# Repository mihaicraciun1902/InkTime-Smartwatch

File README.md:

# ⌚ InkTime: Open-Source Hackable Smartwatch

**InkTime** is an affordable, open-source smartwatch powered by the Nordic nRF52840 SoC and an ultra-low-power e-paper display. It is designed from the ground up to be highly hackable, easy to manufacture, and power-efficient.

This repository contains all Engineering Validation (EVT) and Design Validation (DVT) files, including schematics, PCB layouts, 3D mechanical models, and manufacturing files.

---

## 🏗️ 1. System Architecture (Block Diagram)

The following diagram illustrates the core components of the InkTime hardware and their data/power relationships:

```text
                     +---------------------------------------------------+
                     |               nRF52840 SoC (U$1)                  |
                     |          ARM Cortex-M4F @ 64 MHz                  |
                     |    BLE 5.0 | 1MB Flash | 256KB RAM | USB 2.0      |
                     +---------------------------------------------------+
                              |                 |                  |
       [ SPI & GPIO ]---------+                 |                  +--------[ I2C Bus ]
       |                                        |                  |
+-------------------+                           |           +-------------------+
| E-Paper Display   |                           |           | BQ25180 (Charger) |<-- USB VBUS
| 24-pin FPC (J2)   |                           |           +-------------------+
+-------------------+       [ Push Buttons ]----+           | MAX17048 (Fuel)   |<-- LiPo Cell
                            | SW_UP (P0.13)     |           +-------------------+
+-------------------+       | SW_ENT (P0.14)    |           | BMA423 (IMU)      |
| Power Management  |       | SW_DN (P1.02)     |           +-------------------+
| RT6160A 3.3V Reg. |       +-------------------+           | DRV2605 (Haptic)  |
+-------------------+                                       +-------------------+
```

## 🧩 2. Hardware Implementation & Functionality

The hardware is designed on a 1mm thick, 2-layer PCB to fit strictly within the mechanical constraints of the provided case. All component placement is restricted to the TOP layer, with dual ground planes and extensive via stitching.

### Core Processing & Connectivity (nRF52840)

The heart of the watch is the nRF52840-QIAA. It handles all BLE 5.0 communication, USB 2.0 Full-Speed interfacing, and peripheral management.

- **Clocks:** Requires a 32 MHz crystal (X1) for the RF HFXO and a 32.768 kHz crystal (X2) for the RTC/LFXO deep sleep timekeeping.
- **RF Layout:** The 2.4 GHz chip antenna (Johanson 2450AT18B100E) is edge-mounted. Per Nordic guidelines, the PCB is physically cut out directly beneath the antenna, with a strict keepout zone (no copper, no routing).

### Display System

We utilize an e-paper display connected via a 24-pin 0.5mm FPC connector.

- **Interface:** 4-wire SPI + GPIO control (DC, RST, BUSY).
- **Power:** Driven by an independent 3.3V boost converter (L1). Power is gated by a P-channel MOSFET (Q1) via the `EPD_PWR` pin, ensuring zero current draw when the display is not refreshing.

### Power Management & Battery (BQ25180 + RT6160A)

- **Charging:** The BQ25180 manages charging from the USB-C VBUS. It is compact and entirely I2C-configurable. The charge current is hardware-set to 100mA via a 10kΩ resistor.
- **Regulation:** The RT6160A buck-boost converter takes the variable LiPo voltage (3.0V - 4.2V) and provides a stable 3.3V system rail.
- **Clearance hack:** To meet strict Z-axis constraints of the case, the JST connector was omitted; the LiPo cell is soldered directly to `TP_VBAT` and `TP_BAT_GND`.

### Sensors & Actuators

- **IMU (BMA423):** A 3-axis accelerometer with a built-in hardware step counter and wrist-tilt detection. It uses hardware interrupts (`IMU_INT1`, `IMU_INT2`) to wake the nRF from deep sleep, saving processing power.
- **Haptics (DRV2605):** Drives an ERM/LRA vibration motor. The `HAPTIC_EN` pin physically disables the driver during sleep to eliminate quiescent current leakage.

## 📌 3. nRF52840 Pin Mapping

Pins were carefully selected to group peripheral buses (like SPI and I2C) physically close to their target ICs, minimizing trace lengths.

| Pin                     | Signal            | Destination      | Function & Justification |
|-------------------------|-------------------|------------------|--------------------------|
| P0.02                   | SCK               | EPD (J2)         | SPI Clock. SPIM is remappable; chosen for routing ease. |
| P0.03                   | MOSI              | EPD (J2)         | SPI Data Out. Grouped with SCK to minimize trace length. |
| P0.05                   | EPD_CS            | EPD (J2)         | SPI Chip Select for e-paper. |
| P0.06                   | SDA               | I2C Bus          | I2C Data. Placed close to BQ25180 & BMA423 to keep traces short. |
| P0.07                   | SCL               | I2C Bus          | I2C Clock. |
| P0.08                   | IMU_INT1          | BMA423           | Hardware wake interrupt from accelerometer. |
| P0.11                   | PMIC_INT          | BQ25180          | Interrupt for battery charge state changes. |
| P0.12                   | HAPTIC_EN         | DRV2605          | GPIO output to hard-disable haptic driver during sleep. |
| P0.13 / P0.14 / P1.02   | SW_UP / ENT / DN  | Tactile Switches | GPIO inputs with hardware debouncing (10kΩ pull-up + 1µF low-pass). |
| P1.01                   | EPD_PWR           | Q1 Gate          | EPD power rail enable switch. |

## 🔋 4. Power Consumption Analysis

The system is highly optimized for deep sleep. Based on component datasheets, estimated battery life on a 180mAh LiPo cell is approximately 5-7 days.

| Mode                  | nRF52840 | Display | Sensors/Other | Total |
|-----------------------|----------|---------|---------------|-------|
| System OFF (Sleep)    | 2.5 µA   | 0 mA    | 0.5 µA        | ~3 µA |
| BLE Advertising (1s)  | ~15 mA   | 0 mA    | 0.13 mA       | ~15 mA |
| Display Refresh       | ~3 mA    | ~30 mA  | 0.13 mA       | ~33 mA |
| Haptic Feedback       | ~5 mA    | 0 mA    | ~60 mA        | ~65 mA |

## 🧾 5. Bill of Materials (BOM)

Updated from Fusion Hub partlist export (Project: **Proiect TSC**, Board: **PCB**, Date: **21/04/2026 4:52 PM**).

| Qty | Value / MPN | Device / Package | Parts | Description |
|-----|-------------|------------------|-------|-------------|
| 1 | ESP32_C6_LIBRARY_7_JUMPER_SJ | ESP32_C6_LIBRARY_7_JUMPER_SJ | SJ1 | SMD solder jumper |
| 3 | 0 / CPF0201D7K68C1 | CPF0201D7K68C1_0201 | R2, R3, R4 | 7.68k thin film resistor, 0201 |
| 2 | 0.1uF / GRM011R60J152KE01L | CAPC0201X13N | C23, C42 | Murata capacitor |
| 3 | 0.1uF | NORDIC_NRF_3_RESC0201_L | C27, C34, EPD_C5 | Generic chip capacitor |
| 1 | 0.47 / CPF0201D7K68C1 | CPF0201D7K68C1_0201 | R1_EP_DR | 0201 thin film resistor |
| 1 | 1.0uF | NORDIC_NRF_3_RESC0201_L | C15 | Generic chip capacitor |
| 5 | 100nF | NORDIC_NRF_3_RESC0201_L | C5, C7, C8, C12, C19 | Generic chip capacitor |
| 1 | 100pF | NORDIC_NRF_3_RESC0201_L | C11 | Generic chip capacitor |
| 2 | 10K / CPF0201D7K68C1 | CPF0201D7K68C1_0201 | R2_EP_DR, R_PWR_EPD | 0201 thin film resistor |
| 4 | 10k / CPF0201D7K68C1 | CPF0201D7K68C1_0201 | R5, R7, R8, R9 | 0201 thin film resistor |
| 3 | 10uF | NORDIC_NRF_3_RESC0201_L | C1-EP-DR, C24, C39 | Generic chip capacitor |
| 1 | 10uH | NORDIC_NRF_2_RESC0402_L | L2 | Generic chip inductor |
| 4 | 12pF | NORDIC_NRF_3_RESC0201_L | C1, C2, C17, C18 | Generic chip capacitor |
| 1 | 15nH | NORDIC_NRF_2_RESC0402_L | L3 | Generic chip inductor |
| 2 | 1pF | NORDIC_NRF_3_RESC0201_L | C3, C4 | Generic chip capacitor |
| 2 | 1uF / GRM011R60J152KE01L | CAPC0201X13N | C37, C38 | Murata capacitor |
| 9 | 1uF | NORDIC_NRF_3_RESC0201_L | EPD_C1, EPD_C2, EPD_C6, EPD_C7, EPD_C8, EPD_C9, EPD_C10, EPD_C11, EPD_C12 | Generic chip capacitor |
| 4 | 1uF | NORDIC_NRF_3_RESC0402_L | C29, C30, C31, C32 | Generic chip capacitor |
| 1 | 2.2 / CPF0201D7K68C1 | CPF0201D7K68C1_0201 | R_TYPE_SEL | 0201 thin film resistor |
| 3 | EVP-AKE31A | SW_EVP-AKE31A_PAN | SW_DN, SW_ENT, SW_UP | Panasonic tactile switch |
| 1 | DMG2305UX-7 | SOT23-3 | Q1 | P-channel MOSFET (20V/4.2A/52mΩ) |
| 2 | 22uF | NORDIC_NRF_3_RESC0201_L | C25, C33 | Generic chip capacitor |
| 1 | 3.9nH | NORDIC_NRF_2_RESC0201_M | L1 | Generic chip inductor |
| 1 | 9HT10-32.768KDZF-T | XTAL330X1051X90N | X2 | 32.768kHz crystal |
| 1 | 32MHz | NORDIC_NRF_BT-XTAL_2016_N | X1 | 32MHz crystal |
| 2 | 3k3 / CPF0201D7K68C1 | CPF0201D7K68C1_0201 | R17, R18 | 0201 thin film resistor |
| 6 | 4.7uF | NORDIC_NRF_3_RESC0201_L | C2-EP-DR, C6, C14, C20, C21, C43 | Generic chip capacitor |
| 1 | 2450AT18B100E | ANTC3216X140N | ANT1 | 2.45GHz chip antenna |
| 1 | 47nF | NORDIC_NRF_3_RESC0201_L | C16 | Generic chip capacitor |
| 1 | 744043680 | IND_4828-WE-TPC_WRE | L5 | Wurth inductor, 48uH |
| 1 | 503480-2400 | 5034802400 | J1 | 24-pin 0.5mm FPC connector |
| 2 | 5k1 / CPF0201D7K68C1 | CPF0201D7K68C1_0201 | R1_USB, R2_USB | 0201 thin film resistor |
| 1 | 820pF | NORDIC_NRF_3_RESC0201_L | C9 | Generic chip capacitor |
| 1 | BMA423 | BMA423_BMA423 | IC3 | 3-axis accelerometer |
| 1 | BQ25180YBGR | BGA8C40P2X4_100X155X50 | IC1 | Li-ion/LiFePO4 charger IC |
| 1 | FTC252012SR47MBCA | INDC2016X100N | L7 | 0.47uH inductor |
| 14 | HECTOR_WATCH_1_TPTP20R | HECTOR_WATCH_1_TP20R | TP_3.3V, TP_3V3, TP_BAT_GND, TP_GND, TP_ON, TP_OP, TP_RESET, TP_SCL, TP_SDA, TP_SWDIO, TP_SWD_CLK, TP_SWO, TP_VBAT, TP_VREG | Test pads |
| 1 | KH-TYPE-C-16P | KH-TYPE-C-16P_KINGHELM_KH-TYPE-C-16P | J4 | USB-C 16-pin connector |
| 1 | MAX17048G+T10 | SON50P200X200X80-9N | U3 | 1-cell/2-cell fuel gauge |
| 3 | MBR0530 | SOD3716X135N | D2, D4, D5 | Schottky diode 30V 0.5A |
| 3 | N.C. | NORDIC_NRF_3_RESC0201_L | C10, C13, C22 | DNI capacitor footprints |
| 1 | NRF52840_QF | AQFN50P700X700X85_HS-74N | U1 | nRF52840 SoC |
| 1 | RT6160AWSC | BGA15C40P3X5_140X230X60 | IC9 | Buck-boost regulator |
| 1 | DRV2605YZFR | BGA9C50P3X3_144X144X62 | IC2 | Haptic driver |
| 1 | SI1308EDL-T1-GE3 | SOT65P210X110-3N | Q3 | N-channel MOSFET |
| 1 | TC2030-IDC | TC2030IDC | J2 | 6-pos cable adapter |
| 1 | USBLC6-2SC6Y | SOT95P280X145-6N | D3 | USB ESD TVS protection array |

## 🛠️ 6. Design Log & Constraint Compliance (Review Notes)

This design strictly follows the DVT guidelines and mechanical constraints. Below are key design decisions and ignored rule exceptions intended for the reviewer:

- **1mm PCB thickness:** Reduced from standard 1.6mm to ensure vertical mechanical clearance inside the provided STEP case.
- **TOP-layer-only placement:** All SMDs and ICs are strictly placed on the TOP layer. Both layers feature grounded copper pours, heavily via-stitched (especially near the RF path).
- **Trace widths & geometry:** Power nets (`3V3`, `VBAT`, `VBUS`, `VREG`) are routed at 0.3mm. Data signals use 0.15mm. Trace neck-down is only utilized under BGA pads. 90-degree angles were avoided; all corners use 45-degree chamfers.
- **Decoupling proximity:** Every 100nF decoupling capacitor is placed immediately adjacent (within one pad length) to its respective IC power pin on the TOP layer.
- **RF keepout & substrate:** The area under the 2450AT18B100E antenna is entirely void of copper on both layers, and features a physical PCB cutout per Nordic reference design.
- **Accepted ERC warning:** "Only INPUT pins on NET ID" is present but ignored as a known false-positive in the CAD tool, approved by project guidelines.
- **Accepted DRC errors:** Dimension errors near the three tactile buttons and the USB-C aperture are intentional structural slots required for casing alignment.
- **Silkscreen integrity:** Test pads (`TP_3V3`, `TP_SWDIO`, etc.) are clearly labeled in silkscreen. Component values are hidden to maintain a clean, readable layout.

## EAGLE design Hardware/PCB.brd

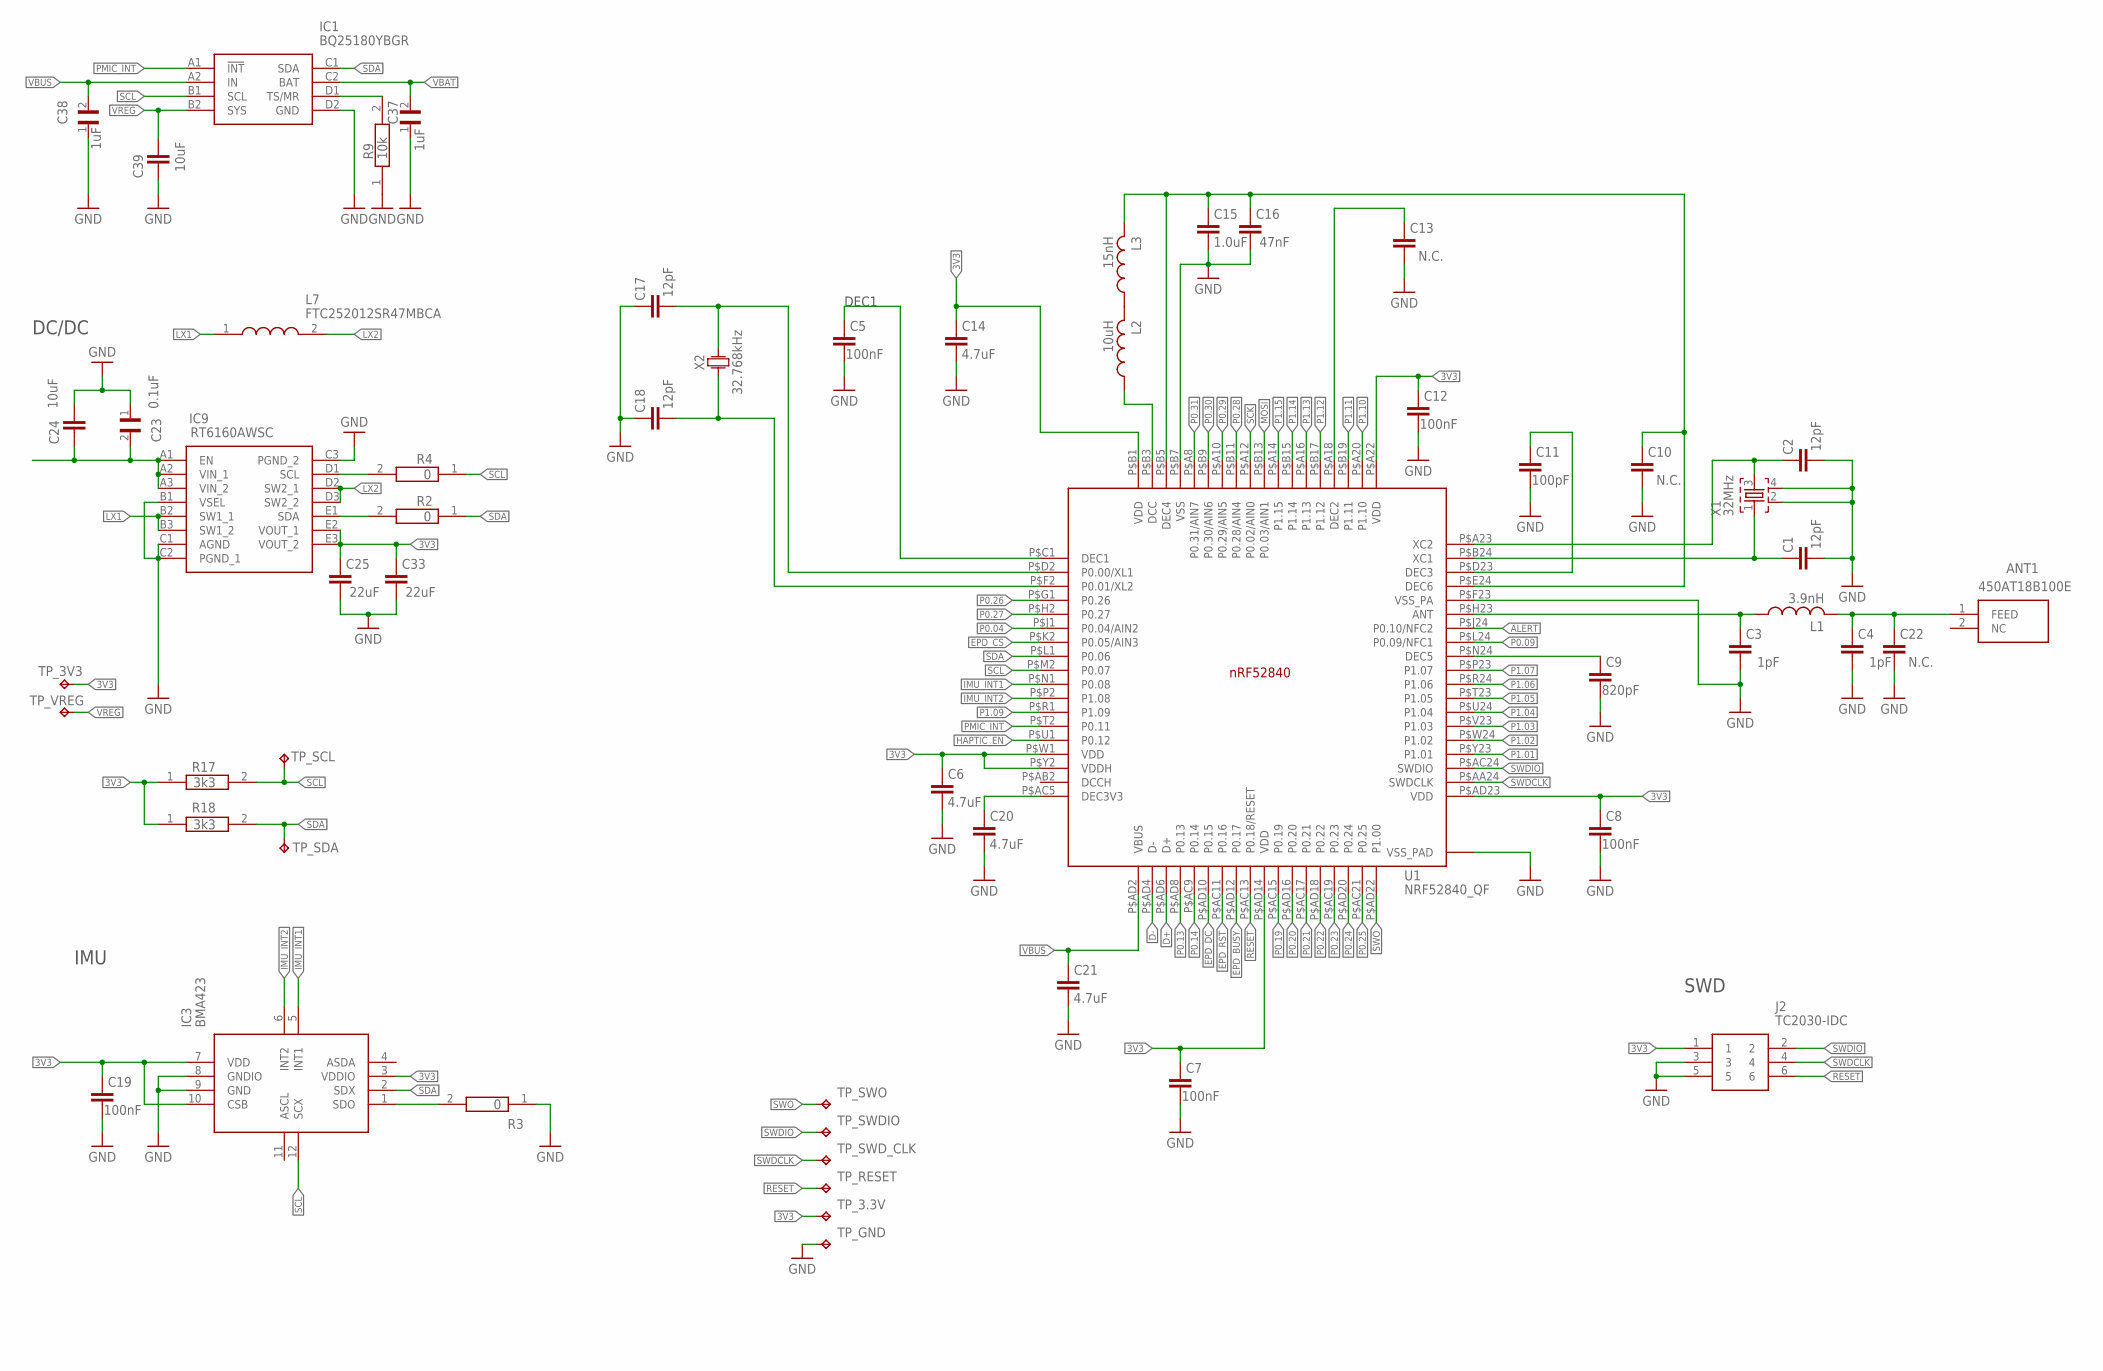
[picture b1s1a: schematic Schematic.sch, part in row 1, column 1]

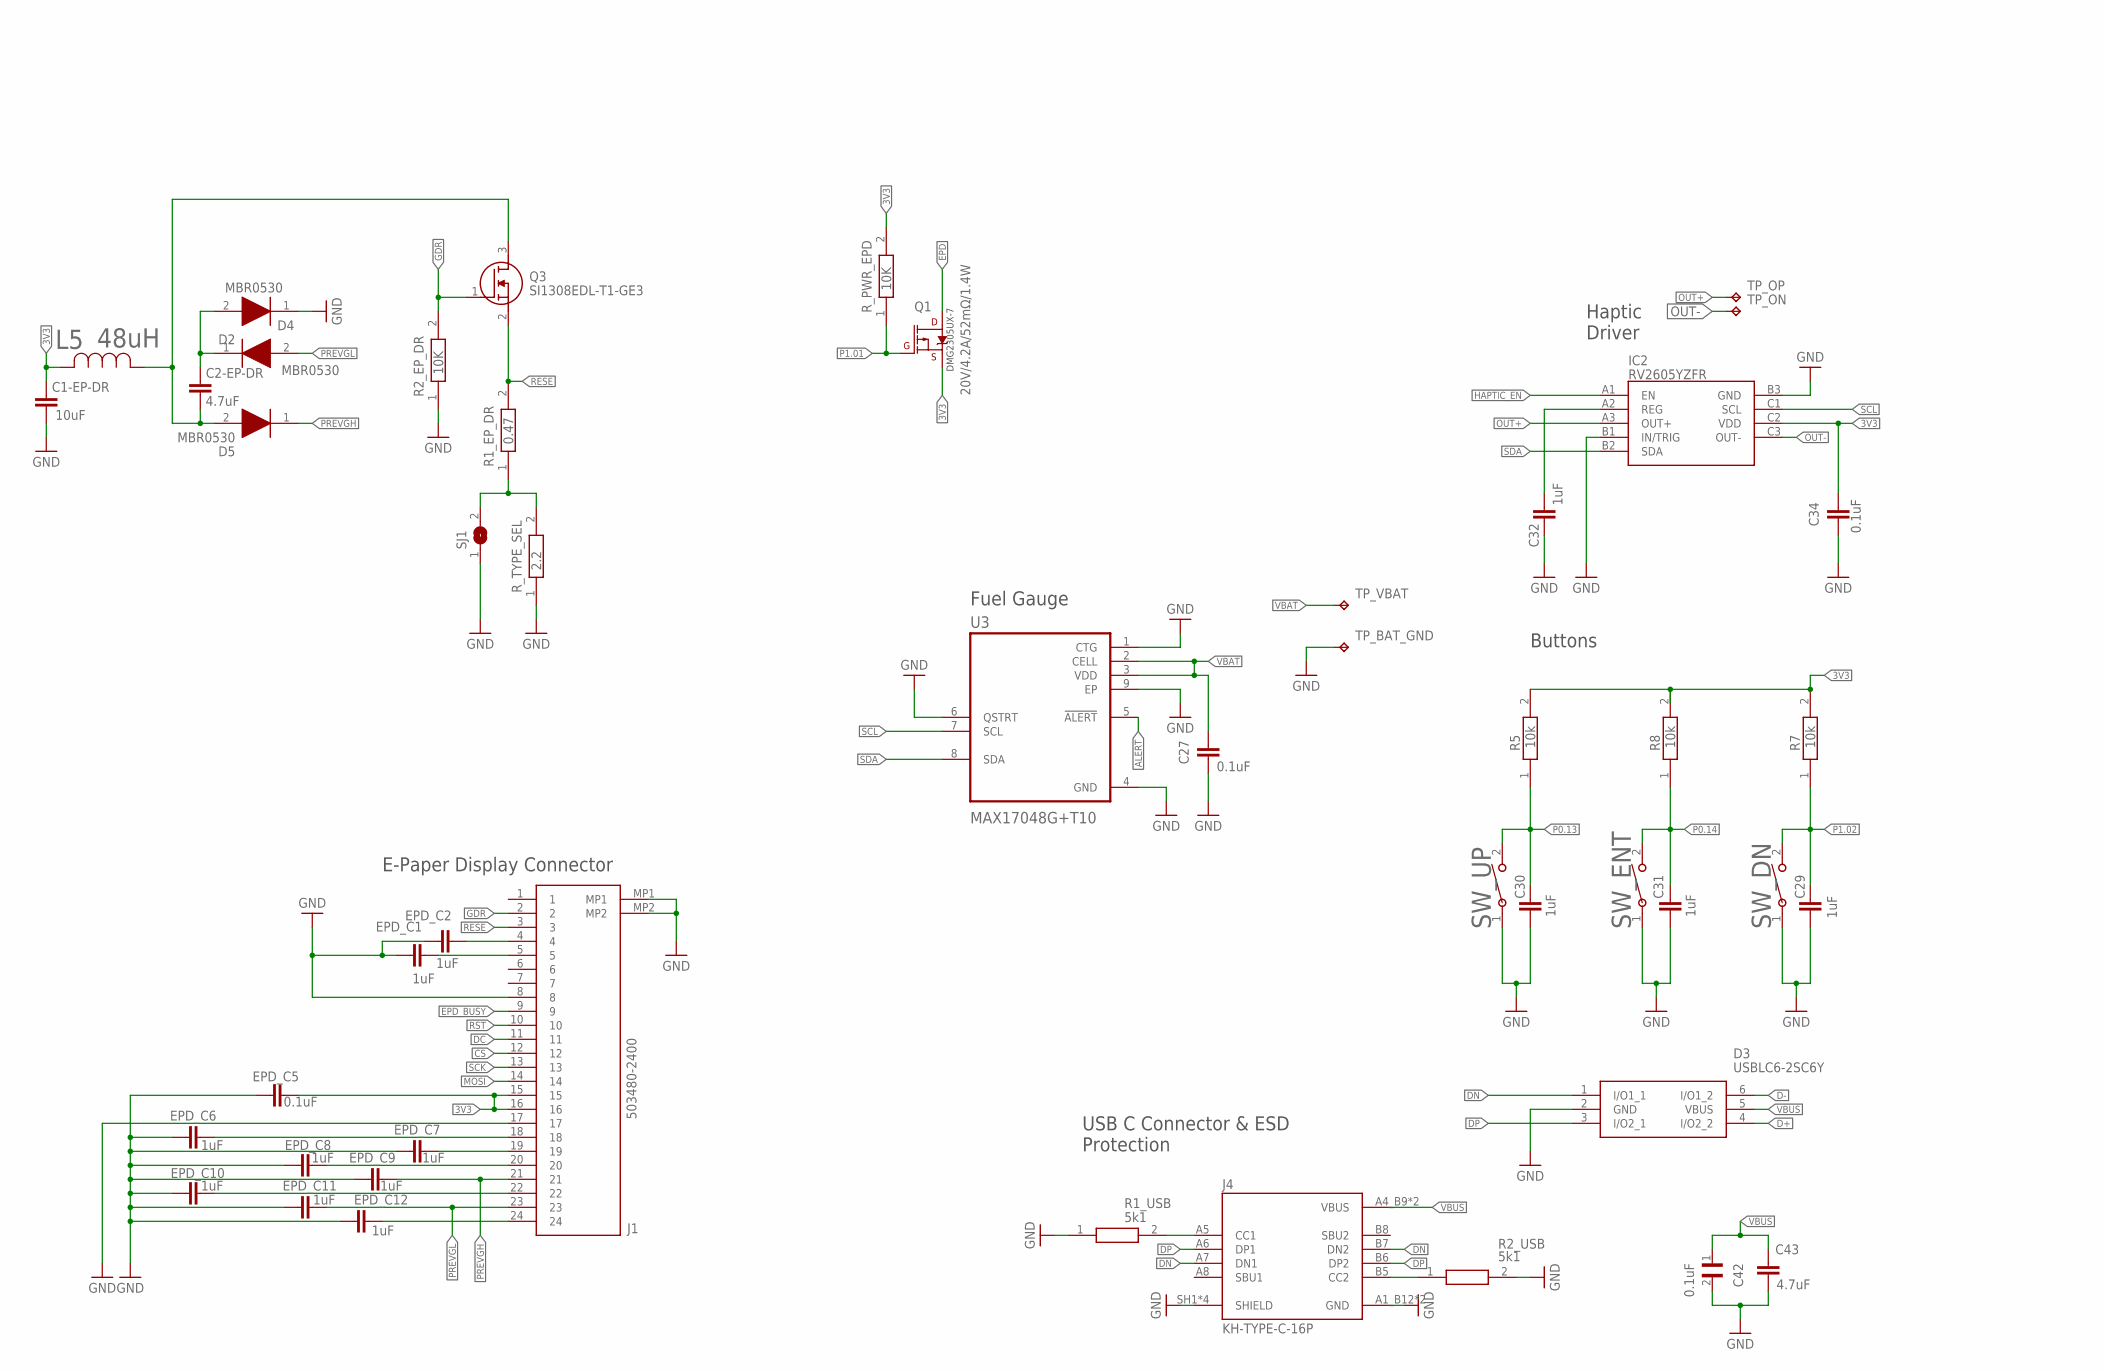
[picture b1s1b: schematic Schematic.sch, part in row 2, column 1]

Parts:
ANT1: 450AT18B100E; 2450AT18B100E_ANTC3216X140N
C1, C2, C17, C18: 12pF; NORDIC_NRF_3_RESC0201_L
C1-EP-DR, C24, C39: 10uF; NORDIC_NRF_3_RESC0201_L
C2-EP-DR, C6, C14, C20, C21, C43: 4.7uF; NORDIC_NRF_3_RESC0201_L
C3, C4: 1pF; NORDIC_NRF_3_RESC0201_L
C5, C7, C8, C12, C19: 100nF; NORDIC_NRF_3_RESC0201_L
C9: 820pF; NORDIC_NRF_3_RESC0201_L
C10, C13, C22: N.C.; NORDIC_NRF_3_RESC0201_L
C11: 100pF; NORDIC_NRF_3_RESC0201_L
C15: 1.0uF; NORDIC_NRF_3_RESC0201_L
C16: 47nF; NORDIC_NRF_3_RESC0201_L
C23, C42: 0.1uF; GRM011R60J152KE01L_2_CAPC0201X13N
C25, C33: 22uF; NORDIC_NRF_3_RESC0201_L
C27, C34: 0.1uF; NORDIC_NRF_3_RESC0201_L
C29, C30, C31, C32: 1uF; NORDIC_NRF_3_RESC0402_L
C37, C38: 1uF; GRM011R60J152KE01L_2_CAPC0201X13N
D2, D4, D5: MBR0530; ESP32_C6_LIBRARY_5_SOD3716X135N
D3: USBLC6-2SC6Y; ESP32_C6_LIBRARY_3_SOT95P280X145-6N
EPD_C1, EPD_C2, EPD_C6, EPD_C7, EPD_C8, EPD_C9, EPD_C10, EPD_C11, EPD_C12: 1uF; NORDIC_NRF_3_RESC0201_L
EPD_C5: 0.1uF; NORDIC_NRF_3_RESC0201_L
IC1: BQ25180YBGR; BQ25180YBGR_BGA8C40P2X4_100X155X50
IC2: RV2605YZFR; DRV2605YZFR_BGA9C50P3X3_144X144X62
IC3: BMA423; BMA423_BMA423
IC9: RT6160AWSC; RT6160AWSC_BGA15C40P3X5_140X230X60
J1: 503480-2400; 503480-2400_5034802400
J2: TC2030-IDC; TC2030-IDC_TC2030IDC
J4: KH-TYPE-C-16P; KH-TYPE-C-16P_KINGHELM_KH-TYPE-C-16P
L1: 3.9nH; NORDIC_NRF_2_RESC0201_M
L2: 10uH; NORDIC_NRF_2_RESC0402_L
L3: 15nH; NORDIC_NRF_2_RESC0402_L
L5: 48uH; ESP32_C6_LIBRARY_2_IND_4828-WE-TPC_WRE
L7: FTC252012SR47MBCA; MLP2016SR47MT0S1_INDC2016X100N
Q1: 20V/4.2A/52mΩ/1.4W; ESP32_C6_LIBRARY_4_ESP32_C6_LIBRARY_4_ESP32_C6_LIBRARY_4_ES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
Q3: SI1308EDL-T1-GE3; ESP32_C6_LIBRARY_6_SOT65P210X110-3N
R1_EP_DR: 0.47; CPF0201D7K68C1_0201
R1_USB, R2_USB: 5k1; CPF0201D7K68C1_0201
R2, R3, R4: 0; CPF0201D7K68C1_0201
R2_EP_DR: 10K; CPF0201D7K68C1_0201
R5, R7, R8, R9: 10k; CPF0201D7K68C1_0201
R17, R18: 3k3; CPF0201D7K68C1_0201
R_PWR_EPD: 10K; CPF0201D7K68C1_0201
R_TYPE_SEL: 2.2; CPF0201D7K68C1_0201
SJ1: ESP32_C6_LIBRARY_7_JUMPER_SJ
SW_DN: 2025-10-22_07-23-44_LIBRARY_EVP-AKE31ASW_EVP-AKE3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; 2025-10-22_07-23-44_LIBRARY_SW_EVP-AKE31A_PAN
SW_ENT: 2025-10-22_07-23-44_LIBRARY_EVP-AKE31ASW_EVP-AKE3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; 2025-10-22_07-23-44_LIBRARY_SW_EVP-AKE31A_PAN
SW_UP: 2025-10-22_07-23-44_LIBRARY_EVP-AKE31ASW_EVP-AKE3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; 2025-10-22_07-23-44_LIBRARY_SW_EVP-AKE31A_PAN
TP_3.3V, TP_3V3: HECTOR_WATCH_1_TPTP20R; HECTOR_WATCH_1_TP20R
TP_BAT_GND: HECTOR_WATCH_1_TPTP20R; HECTOR_WATCH_1_TP20R
TP_GND: HECTOR_WATCH_1_TPTP20R; HECTOR_WATCH_1_TP20R
TP_ON: HECTOR_WATCH_1_TPTP20R; HECTOR_WATCH_1_TP20R
TP_OP: HECTOR_WATCH_1_TPTP20R; HECTOR_WATCH_1_TP20R
TP_RESET: HECTOR_WATCH_1_TPTP20R; HECTOR_WATCH_1_TP20R
TP_SCL: HECTOR_WATCH_1_TPTP20R; HECTOR_WATCH_1_TP20R
TP_SDA: HECTOR_WATCH_1_TPTP20R; HECTOR_WATCH_1_TP20R
TP_SWDIO: HECTOR_WATCH_1_TPTP20R; HECTOR_WATCH_1_TP20R
TP_SWD_CLK: HECTOR_WATCH_1_TPTP20R; HECTOR_WATCH_1_TP20R
TP_SWO: HECTOR_WATCH_1_TPTP20R; HECTOR_WATCH_1_TP20R
TP_VBAT: HECTOR_WATCH_1_TPTP20R; HECTOR_WATCH_1_TP20R
TP_VREG: HECTOR_WATCH_1_TPTP20R; HECTOR_WATCH_1_TP20R
U1: NRF52840_QF; NORDIC_NRF_4_AQFN50P700X700X85_HS-74N
U3: MAX17048G+T10; ESP32_C6_LIBRARY_SON50P200X200X80-9N
X1: 32MHz; NORDIC_NRF_BT-XTAL_2016_N
X2: 32.768kHz; XTAL330X1051X90N

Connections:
3V3: C1-EP-DR.2, C6.2, C7.2, C8.2, C12.2, C14.2, C19.2, C25.2, C33.2, C34.1, EPD_C5.2, IC2.C2 (VDD), IC3.3 (VDDIO), IC3.7 (VDD), IC3.10 (CSB), IC9.E2 (VOUT_1), IC9.E3 (VOUT_2), J1.15, J1.16, J2.1, L5.2, Q1.2 (S), R5.2, R7.2, R8.2, R17.1, R18.1, R_PWR_EPD.2, TP_3.3V.TP, TP_3V3.TP, U1.P$A22 (VDD), U1.P$AD14 (VDD), U1.P$AD23 (VDD), U1.P$B1 (VDD), U1.P$W1 (VDD), U1.P$Y2 (VDDH)
ALERT: U1.P$J24 (P0.10/NFC2), U3.5 (!ALERT)
CS: J1.12
D+: D3.4 (I/O2_2), U1.P$AD6 (D+)
D-: D3.6 (I/O1_2), U1.P$AD4 (D-)
DC: J1.11
DN: D3.1 (I/O1_1), J4.A7 (DN1), J4.B7 (DN2)
DP: D3.3 (I/O2_1), J4.A6 (DP1), J4.B6 (DP2)
EPD: Q1.3 (D)
EPD_BUSY: J1.9, U1.P$AD12 (P0.17)
EPD_CS: U1.P$K2 (P0.05/AIN3)
EPD_DC: U1.P$AD10 (P0.15)
EPD_RST: U1.P$AC11 (P0.16)
GDR: J1.2, Q3.1 (G), R2_EP_DR.2
GND: C1.1, C1-EP-DR.1, C2.1, C3.1, C4.1, C5.1, C6.1, C7.1, C8.1, C9.1, C10.1, C11.1, C12.1, C13.1, C14.1, C15.1, C16.1, C17.2, C18.2, C19.1, C20.1, C21.1, C22.1, C23.1, C24.2, C25.1, C27.2, C29.2, C30.2, C31.2, C32.2, C33.1, C34.2, C37.1, C38.1, C39.1, C42.2, C43.2, D2.1 (K), D3.2 (GND), EPD_C1.1, EPD_C2.1, EPD_C5.1, EPD_C6.1, EPD_C7.1, EPD_C8.1, EPD_C9.1, EPD_C10.1, EPD_C11.1, EPD_C12.1, IC1.D2 (GND), IC2.B1 (IN/TRIG), IC2.B3 (GND), IC3.8 (GNDIO), IC3.9 (GND), IC9.B1 (VSEL), IC9.C1 (AGND), IC9.C2 (PGND_1), IC9.C3 (PGND_2), J1.8, J1.17, J1.MP1, J1.MP2, J2.3, J2.5, J4.A1_B12 (GND), J4.A12_B1 (GND), J4.SH1 (SHIELD), J4.SH2 (SHIELD), J4.SH3 (SHIELD), J4.SH4 (SHIELD), R1_USB.1, R2_EP_DR.1, R2_USB.2, R3.1, R9.1, R_TYPE_SEL.1, SJ1.1, SW_DN.1, SW_ENT.1, SW_UP.1, TP_BAT_GND.TP, TP_GND.TP, U1.P$74 (VSS_PAD), U1.P$75 (VSS_PAD), U1.P$76 (VSS_PAD), U1.P$77 (VSS_PAD), U1.P$78 (VSS_PAD), U1.P$79 (VSS_PAD), U1.P$80 (VSS_PAD), U1.P$81 (VSS_PAD), U1.P$82 (VSS_PAD), U1.P$83 (VSS_PAD), U1.P$84 (VSS_PAD), U1.P$85 (VSS_PAD), U1.P$86 (VSS_PAD), U1.P$87 (VSS_PAD), U1.P$88 (VSS_PAD), U1.P$89 (VSS_PAD), U1.P$90 (VSS_PAD), U1.P$B7 (VSS), U1.P$F23 (VSS_PA), U3.1 (CTG), U3.4 (GND), U3.6 (QSTRT), U3.9 (EP), X1.2, X1.4
HAPTIC_EN: IC2.A1 (EN), U1.P$U1 (P0.12)
IMU_INT1: IC3.5 (INT1), U1.P$N1 (P0.08)
IMU_INT2: IC3.6 (INT2), U1.P$P2 (P1.08)
LX1: IC9.B2 (SW1_1), IC9.B3 (SW1_2), L7.1
LX2: IC9.D2 (SW2_1), IC9.D3 (SW2_2), L7.2
MOSI: J1.14, U1.P$B13 (P0.03/AIN1)
unnamed: ANT1.1 (FEED), C4.2, C22.2, L1.2
unnamed: L2.2, L3.1
unnamed: J4.A5 (CC1), R1_USB.2
unnamed: C32.1, IC2.A2 (REG)
unnamed: C31.1, R8.1, SW_ENT.2
unnamed: C29.1, R7.1, SW_DN.2
unnamed: EPD_C6.2, J1.18
unnamed: EPD_C7.2, J1.19
unnamed: EPD_C2.2, J1.4
unnamed: EPD_C8.2, J1.20
unnamed: J4.B5 (CC2), R2_USB.1
unnamed: EPD_C1.2, J1.5
unnamed: C2-EP-DR.1, D5.2 (A), L5.1, Q3.3 (D)
unnamed: EPD_C10.2, J1.22
unnamed: C2-EP-DR.2, D2.2 (A), D4.1 (K)
unnamed: EPD_C12.2, J1.24
unnamed: R1_EP_DR.1, R_TYPE_SEL.2, SJ1.2
unnamed: IC9.D1 (SCL), R4.2
unnamed: IC9.E1 (SDA), R2.2
unnamed: L2.1, U1.P$B3 (DCC)
unnamed: C23.2, C24.1, IC9.A1 (EN), IC9.A2 (VIN_1), IC9.A3 (VIN_2)
unnamed: IC3.1 (SDO), R3.2
unnamed: C13.2, U1.P$A18 (DEC2)
unnamed: C10.2, C15.2, C16.2, L3.2, U1.P$B5 (DEC4), U1.P$E24 (DEC6)
unnamed: C5.2, U1.P$C1 (DEC1)
unnamed: C17.1, U1.P$D2 (P0.00/XL1), X2.2
unnamed: IC1.D1 (TS/MR), R9.2
unnamed: C18.1, U1.P$F2 (P0.01/XL2), X2.1
unnamed: C20.2, U1.P$AC5 (DEC3V3)
unnamed: C9.2, U1.P$N24 (DEC5)
unnamed: C11.2, U1.P$D23 (DEC3)
unnamed: C3.2, L1.1, U1.P$H23 (ANT)
unnamed: C1.2, U1.P$B24 (XC1), X1.1
unnamed: C2.2, U1.P$A23 (XC2), X1.3
OUT+: IC2.A3 (OUT+), TP_OP.TP
OUT-: IC2.C3 (OUT-), TP_ON.TP
P0.04: U1.P$J1 (P0.04/AIN2)
P0.09: U1.P$L24 (P0.09/NFC1)
P0.13: C30.1, R5.1, SW_UP.2, U1.P$AD8 (P0.13)
P0.14: U1.P$AC9 (P0.14)
P0.19: U1.P$AC15 (P0.19)
P0.20: U1.P$AD16 (P0.20)
P0.21: U1.P$AC17 (P0.21)
P0.22: U1.P$AD18 (P0.22)
P0.23: U1.P$AC19 (P0.23)
P0.24: U1.P$AD20 (P0.24)
P0.25: U1.P$AC21 (P0.25)
P0.26: U1.P$G1 (P0.26)
P0.27: U1.P$H2 (P0.27)
P0.28: U1.P$B11 (P0.28/AIN4)
P0.29: U1.P$A10 (P0.29/AIN5)
P0.30: U1.P$B9 (P0.30/AIN6)
P0.31: U1.P$A8 (P0.31/AIN7)
P1.01: Q1.1 (G), R_PWR_EPD.1, U1.P$Y23 (P1.01)
P1.02: U1.P$W24 (P1.02)
P1.03: U1.P$V23 (P1.03)
P1.04: U1.P$U24 (P1.04)
P1.05: U1.P$T23 (P1.05)
P1.06: U1.P$R24 (P1.06)
P1.07: U1.P$P23 (P1.07)
P1.09: U1.P$R1 (P1.09)
P1.10: U1.P$A20 (P1.10)
P1.11: U1.P$B19 (P1.11)
P1.12: U1.P$B17 (P1.12)
P1.13: U1.P$A16 (P1.13)
P1.14: U1.P$B15 (P1.14)
P1.15: U1.P$A14 (P1.15)
PMIC_INT: IC1.A1 (!INT), U1.P$T2 (P0.11)
PREVGH: D5.1 (K), EPD_C9.2, J1.21
PREVGL: D4.2 (A), EPD_C11.2, J1.23
RESE: J1.3, Q3.2 (S), R1_EP_DR.2
RESET: J2.6, TP_RESET.TP, U1.P$AC13 (P0.18/RESET)
RST: J1.10
SCK: J1.13, U1.P$A12 (P0.02/AIN0)
SCL: IC1.B1 (SCL), IC2.C1 (SCL), IC3.12 (SCX), R4.1, R17.2, TP_SCL.TP, U1.P$M2 (P0.07), U3.7 (SCL)
SDA: IC1.C1 (SDA), IC2.B2 (SDA), IC3.2 (SDX), R2.1, R18.2, TP_SDA.TP, U1.P$L1 (P0.06), U3.8 (SDA)
SWDCLK: J2.4, TP_SWD_CLK.TP, U1.P$AA24 (SWDCLK)
SWDIO: J2.2, TP_SWDIO.TP, U1.P$AC24 (SWDIO)
SWO: TP_SWO.TP, U1.P$AD22 (P1.00)
VBAT: C27.1, C37.2, IC1.C2 (BAT), TP_VBAT.TP, U3.2 (CELL), U3.3 (VDD)
VBUS: C21.2, C38.2, C42.1, C43.1, D3.5 (VBUS), IC1.A2 (IN), J4.A4_B9 (VBUS), J4.A9_B4 (VBUS), U1.P$AD2 (VBUS)
VREG: C39.2, IC1.B2 (SYS), TP_VREG.TP

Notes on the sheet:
Fuel Gauge
Haptic Driver
Buttons
DMG2305UX-7
USB C Connector & ESD Protection
E-Paper Display Connector
IMU
SWD
DC/DC
DEC1

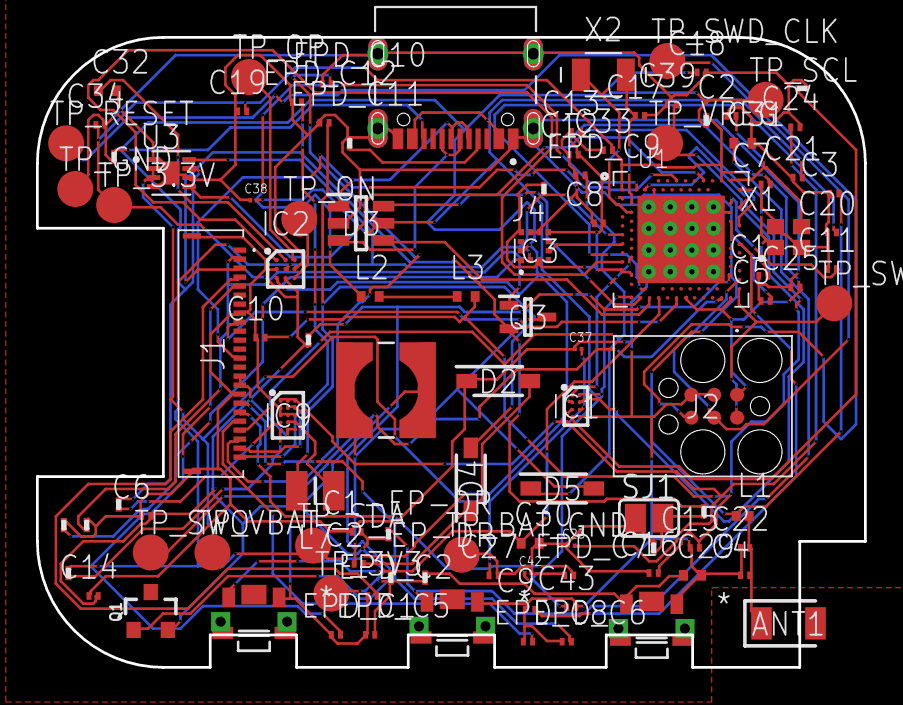
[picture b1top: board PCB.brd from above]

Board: 2 copper layers, 46.0 x 35.0 mm, 105 parts (0 on the bottom side), 67 nets.

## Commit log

2026-04-21 Add files via upload
    updated schematic and pcb
2026-04-21 Enhance README with detailed project information
    Expanded the README to include detailed information about the InkTime smartwatch, including system architecture, hardware implementation, power consumption analysis, and a bill of materials.

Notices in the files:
parts and their libraries:
COPYRIGHT: Copyright (C) 2025 Ultra Librarian. All rights reserved.
COPYRIGHT: Copyright (C) 2024 Ultra Librarian. All rights reserved.
